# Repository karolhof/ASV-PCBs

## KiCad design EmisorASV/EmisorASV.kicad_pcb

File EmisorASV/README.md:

# Emisor ASV - ESP32 DevKit y LoRa

Esquema con cables continuos y PCB de una cara. El ESP32 se conecta al LoRa por SPI y control; no hay conexiones UART a STM32. Alimentación por USB del DevKit desde el celular en modo host OTG.

## Archivos

- `EmisorASV.kicad_pro`: proyecto KiCad 10.
- `EmisorASV.kicad_sch`: esquema conectado.
- `EmisorASV.kicad_pcb`: PCB principal, cobre solo B.Cu.
- `EmisorASV_Vista_puentes.kicad_pcb`: copia para mostrar alambres en F.Cu; no fabricar esa cara.
- `documentacion/EmisorASV.pdf`: esquema.
- `documentacion/PCB_Emisor_montaje.pdf`: guía de montaje.
- `documentacion/PCB_Impresion_1a1.pdf`: cobre y puentes a escala real, con agujeros.
- `documentacion/Lista_de_materiales.md`: materiales y dimensiones.
- `documentacion/ERC.rpt`, `DRC.json`, `verificar_diseno.py`: verificaciones.
- `fabricacion/Gerber/`: fabricación de una cara; no contiene F.Cu.

## Alimentación y montaje

USB alimenta el ESP32; su pin 5V lleva esa alimentación a U2, LD1117V33 TO-220, que genera 3,3 V exclusivamente para el LoRa. Pinout U2: 1 GND, 2 OUT, 3 IN; la aleta es OUT. No conectar el 3V3 del DevKit a LORA_3V3. No conectar batería de 12 V a este emisor.

C4 47 µF junto al pin 5V del ESP32. C5 100 nF junto a IN/GND de U2. C6 22 µF junto a OUT/GND de U2. C7 100 nF y C8 10 µF junto al LoRa, con pistas y retornos locales cortos. Todo THT salvo el módulo LoRa, montado por debajo.

Antena actual de resorte: J4 y JP2 sin montar. ANT del módulo es pad 16, separado de GND. La ruta SMA es una reserva que requiere validación RF antes de usar antena externa.

El celular debe tener modo host USB OTG y suministrar corriente suficiente. Compatibilidad y autonomía dependen del teléfono/cable y se comprueban en el prototipo. El diseño no incluye firmware ni aplicación del celular.

## Mapa de conexiones, igual al receptor

| Señal | GPIO ESP32 | Pad LoRa |
|---|---:|---:|
| SCK | 18 | 8 |
| MOSI | 23 | 7 |
| MISO | 19 | 6 |
| NSS | 27 | 9 |
| RESET | 14 | 11 |
| DIO0 | 26 | 10 |
| DIO1 | 25 | 2 |
| DIO2 | 33 | 3 |
| VCC | LORA_3V3 | 5 |
| GND | GND | 1, 12, 15 |
| ANT | RF_433 | 16 |

R1/R2 de 10 kΩ mantienen NSS/RESET en alto al arrancar. Los pads LoRa 4, 13, 14 quedan sin conectar. GPIO restantes del ESP32 quedan libres. La huella del ESP32 es la suministrada; la LoRa corresponde a la ya confirmada por el usuario para el receptor. Se respaldaron los archivos anteriores en `documentacion/Emisor_antes_de_actualizar.zip`.

## Fuentes

- [Espressif DevKitC V4: USB, alimentación y pines](https://docs.espressif.com/projects/esp-dev-kits/en/latest/esp32/esp32-devkitc/user_guide.html).
- [ST LD1117: pinout y capacitor de estabilidad](https://www.st.com/resource/en/datasheet/ld1117.pdf).
- ZIP del ESP32 y fotos del módulo aportados por el usuario; huella LoRa confirmada en esta conversación.

Las comprobaciones de software no sustituyen las mediciones de 5 V/3,3 V y el ensayo de transmisión del prototipo. Los scripts de generación sobrescriben colocación y esquema; conservar el diseño final antes de ejecutarlos.

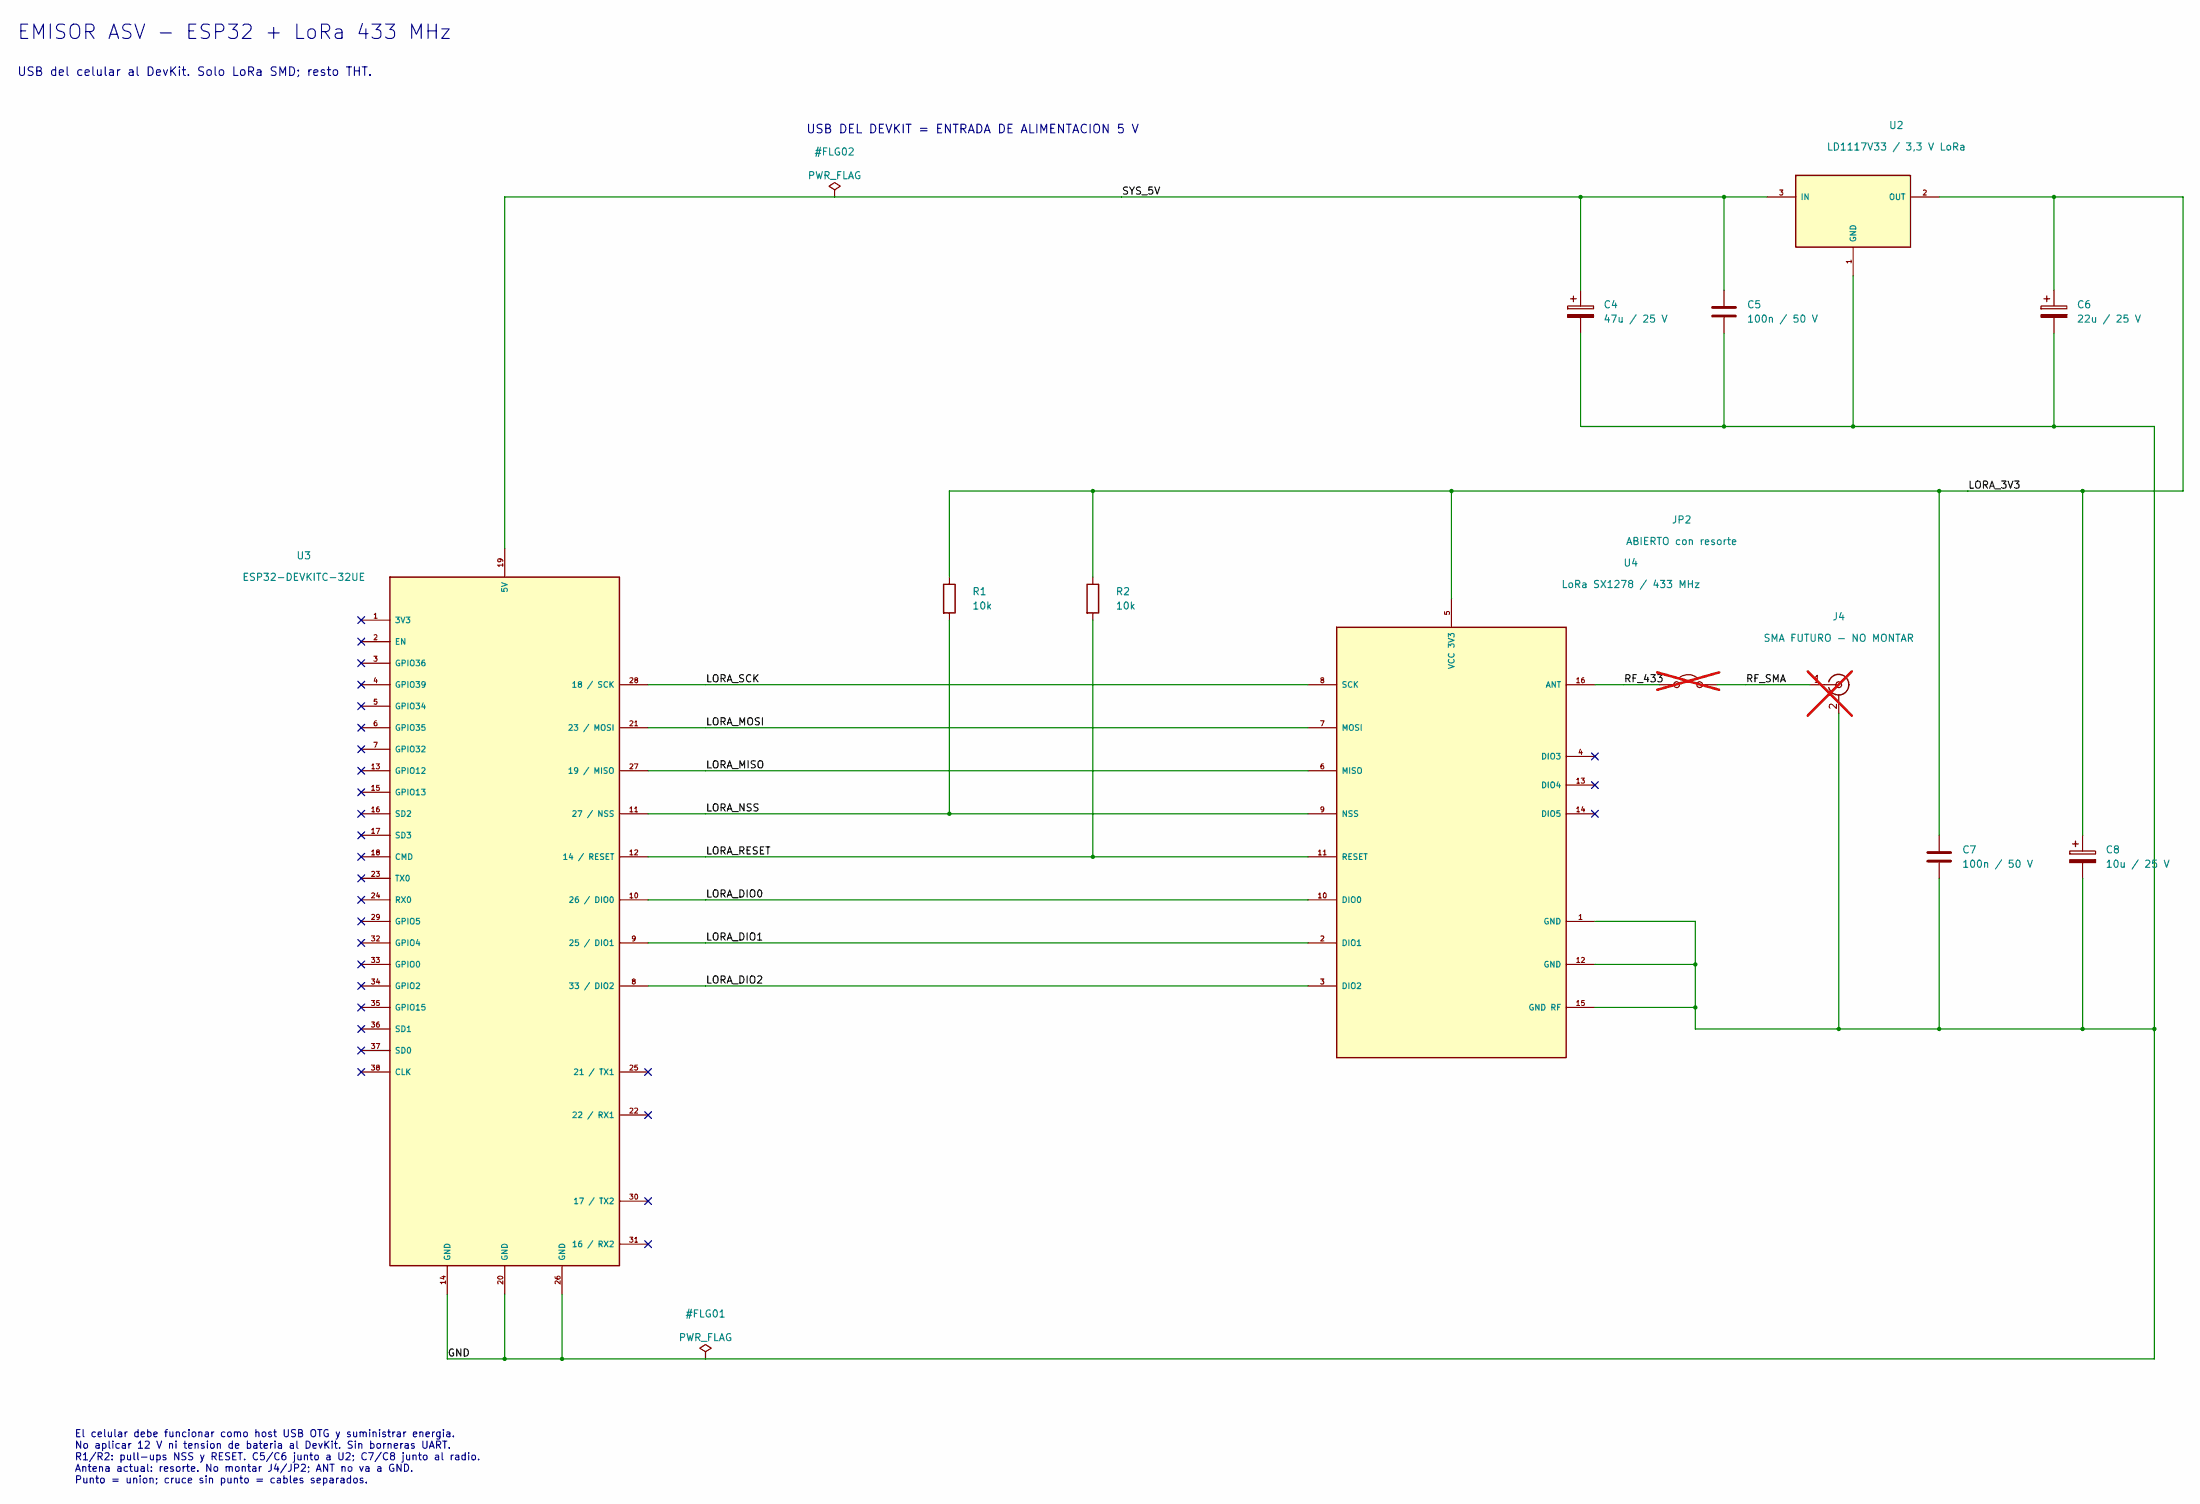
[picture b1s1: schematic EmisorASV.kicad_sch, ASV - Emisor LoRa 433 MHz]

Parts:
C4: 47u / 25 V; CP_Radial_D5.0mm_P2.00mm
C5, C7: 100n / 50 V; C_Disc_D5.0mm_W2.5mm_P5.00mm
C6: 22u / 25 V; CP_Radial_D5.0mm_P2.00mm
C8: 10u / 25 V; CP_Radial_D5.0mm_P2.00mm
J4: SMA FUTURO - NO MONTAR; SMA_Amphenol_132134_Vertical; not fitted
JP2: ABIERTO con resorte; PinHeader_1x02_P2.54mm_Vertical; not fitted
R1, R2: 10k; R_Axial_DIN0207_L6.3mm_D2.5mm_P7.62mm_Horizontal
U2: LD1117V33 / 3,3 V LoRa; TO-220-3_Vertical
U3: ESP32-DEVKITC-32UE; ESPRESSIF_ESP32-DEVKITC-32UE
U4: LoRa SX1278 / 433 MHz; XL1278_SMT_16P_16.5x17mm_P1.27mm

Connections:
/GND: C4.2, C5.2, C6.2, C7.2, C8.2, J4.2 (Ext), U2.1 (GND), U3.14 (GND), U3.20 (GND), U3.26 (GND), U4.1 (GND), U4.12 (GND), U4.15 (GND RF)
/LORA_3V3: C6.1, C7.1, C8.1, R1.1, R2.1, U2.2 (OUT), U4.5 (VCC 3V3)
/LORA_DIO0: U3.10 (26 / DIO0), U4.10 (DIO0)
/LORA_DIO1: U3.9 (25 / DIO1), U4.2 (DIO1); also elsewhere on the board
/LORA_DIO2: U3.8 (33 / DIO2), U4.3 (DIO2); also elsewhere on the board
/LORA_MISO: U3.27 (19 / MISO), U4.6 (MISO)
/LORA_MOSI: U3.21 (23 / MOSI), U4.7 (MOSI)
/LORA_NSS: R1.2, U3.11 (27 / NSS), U4.9 (NSS)
/LORA_RESET: R2.2, U3.12 (14 / RESET), U4.11 (RESET)
/LORA_SCK: U3.28 (18 / SCK), U4.8 (SCK)
/RF_433: JP2.1 (A), U4.16 (ANT)
/RF_SMA: J4.1 (In), JP2.2 (B)
/SYS_5V: C4.1, C5.1, U2.3 (IN), U3.19 (5V)

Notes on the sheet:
EMISOR ASV - ESP32 + LoRa 433 MHz
USB del celular al DevKit. Solo LoRa SMD; resto THT.
USB DEL DEVKIT = ENTRADA DE ALIMENTACION 5 V
El celular debe funcionar como host USB OTG y suministrar energia. No aplicar 12 V ni tension de bateria al DevKit. Sin borneras UART. R1/R2: pull-ups NSS y RESET. C5/C6 junto a U2; C7/C8 junto al radio. Antena actual: resorte. No montar J4/JP2; ANT no va a GND. Punto = union; cruce sin punto = cab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

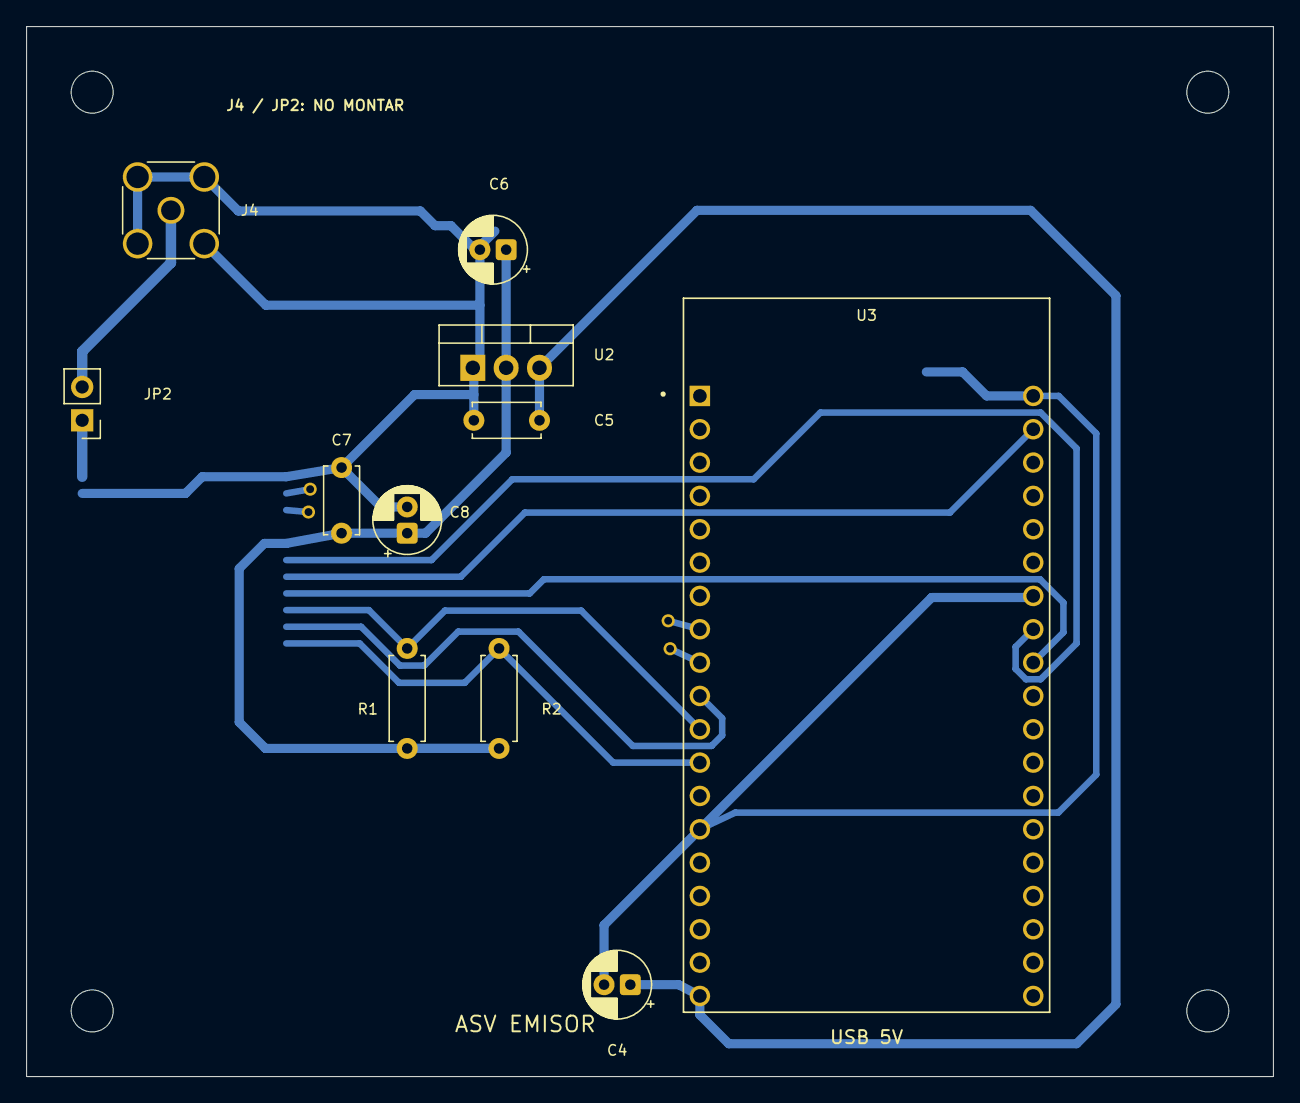
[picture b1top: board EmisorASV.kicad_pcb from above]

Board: 2 copper layers, 95.0 x 80.0 mm, 18 parts (1 on the bottom side), 13 nets.

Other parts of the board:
H1, H2, H3, H4: M3; MountingHole_3.2mm_M3
W1: ALAMBRE AISLADO; Wire_Jumper_W1_30_00mm
W2: ALAMBRE AISLADO; Wire_Jumper_W2_28_63mm

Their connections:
/LORA_DIO1: W1.1; also elsewhere on the board
/LORA_DIO2: W2.1; also elsewhere on the board

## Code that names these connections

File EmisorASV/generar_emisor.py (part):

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put(ldo,'U2','LD1117V33 / 3,3 V LoRa',340.36,45.72,foot='Package_TO_SOT_THT:TO-220-3_Vertical',datasheet='https://www.st.com/resource/en/datasheet/ld1117.pdf',props=[(348,30.48),(348,34.29)])
for ref,x,key,value,foot in [('C4',292.1,'Device:C_Polarized','47u / 25 V',CAP),('C5',317.5,'Device:C','100n / 50 V',CER),('C6',375.92,'Device:C_Polarized','22u / 25 V',CAP)]:
 put(key,ref,value,x,63.5,foot=foot)
route(pp('U3',19),(101.6,43.18),pp('U2',3));mark('U3',19,'SYS_5V');mark('U2',3,'SYS_5V');label('SYS_5V',(210.82,43.18))
for ref in ['C4','C5']:tap(ref,1,'SYS_5V',(pp(ref,1)[0],43.18))
route(pp('U2',2),(398.78,43.18),(398.78,95.25),(180.34,95.25));mark('U2',2,'LORA_3V3')
tap('C6',1,'LORA_3V3',(375.92,43.18));tap('U4',5,'LORA_3V3',(269.24,95.25));label('LORA_3V3',(360.68,95.25))
label('GND',(91.44,248.92));route((91.44,248.92),(393.7,248.92));route((393.7,83.82),(393.7,248.92));route((292.1,83.82),(393.7,83.82))
for ref,pin in [('U2',1),('C4',2),('C5',2),('C6',2)]:tap(ref,pin,'GND',(pp(ref,pin)[0],83.82))
for pin in [14,20,26]:tap('U3',pin,'GND',(pp('U3',pin)[0],248.92))
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 if pin not in instances['U3']['nets']:nc('U3',pin)
put('Connector:Conn_Coaxial','J4','SMA FUTURO - NO MONTAR',337.82,129.54,foot='Connector_Coaxial:SMA_Amphenol_132134_Vertical',props=[(337.82,117.475),(337.82,121.285)])
put(rfjump,'JP2','ABIERTO con resorte',311.15,129.54,foot='Connector_PinHeader_2.54mm:PinHeader_1x02_P2.54mm_Vertical',props=[(310,100.33),(310,104.14)])
link('U4',16,'JP2',1,'RF_433');label('RF_433',(299.72,129.54));link('JP2',2,'J4',1,'RF_SMA');label('RF_SMA',(321.31,129.54));tap('J4',2,'GND',(337.82,190.5))
for ref,x,key,value,foot in [('C7',355.6,'Device:C','100n / 50 V',CER),('C8',381,'Device:C_Polarized','10u / 25 V',CAP)]:
 put(key,ref,value,x,160.02,foot=foot);tap(ref,1,'LORA_3V3',(x,95.25));tap(ref,2,'GND',(x,190.5))
for ref,x,y,net in [('#FLG01',137.16,248.92,'GND'),('#FLG02',160.02,43.18,'SYS_5V')]:
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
